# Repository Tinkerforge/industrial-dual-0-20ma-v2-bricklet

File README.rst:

Industrial Dual 0-20mA Bricklet 2.0
===================================

This repository contains the firmware source code and the hardware design
files. The documentation generator configs can be found at
https://github.com/Tinkerforge/generators

Repository Content
------------------

software/:
 * examples/: Examples for all supported languages
 * build/: Compiled files
 * src/: Source code of firmware
 * Makefile: Makefile to build project

hardware/:
 * Contains KiCad project files and additionally schematics as PDF

datasheets/:
 * Contains datasheets for sensors and complex ICs that are used

Hardware
--------

The hardware is designed with the open source EDA Suite KiCad
(http://www.kicad.org). Before you are able to open the files,
you have to install the Tinkerforge kicad-libraries
(https://github.com/Tinkerforge/kicad-libraries). You can either clone
them directly in hardware/ or clone them in a separate folder and
symlink them into hardware/
(ln -s kicad_path/kicad-libraries project_path/hardware). After that you
can open the .pro file in hardware/ with KiCad and from there view and
modify the schematics and the PCB layout.

Software
--------

If you want to do your own Brick/Bricklet firmware development we highly
recommend that you use our build environment setup script and read the
tutorial (https://www.tinkerforge.com/en/doc/Tutorials/Tutorial_Build_Environment/Tutorial.html).

To compile the C code we recommend you to install the newest GNU Arm Embedded
Toolchain (https://launchpad.net/gcc-arm-embedded/+download).
You also need to install bricklib2 (https://github.com/Tinkerforge/bricklib2).

You can either clone it directly in software/src/ or clone it in a
separate folder and symlink it into software/src/
(ln -s bricklib_path/bricklib2 project_path/software/src/). Finally make sure to
have CMake installed (http://www.cmake.org/cmake/resources/software.html).

After that you can build the firmware by invoking make in software/.
The firmware (.zbin) can then be found in software/build/ and uploaded
with brickv (click button "Flashing" on start screen).

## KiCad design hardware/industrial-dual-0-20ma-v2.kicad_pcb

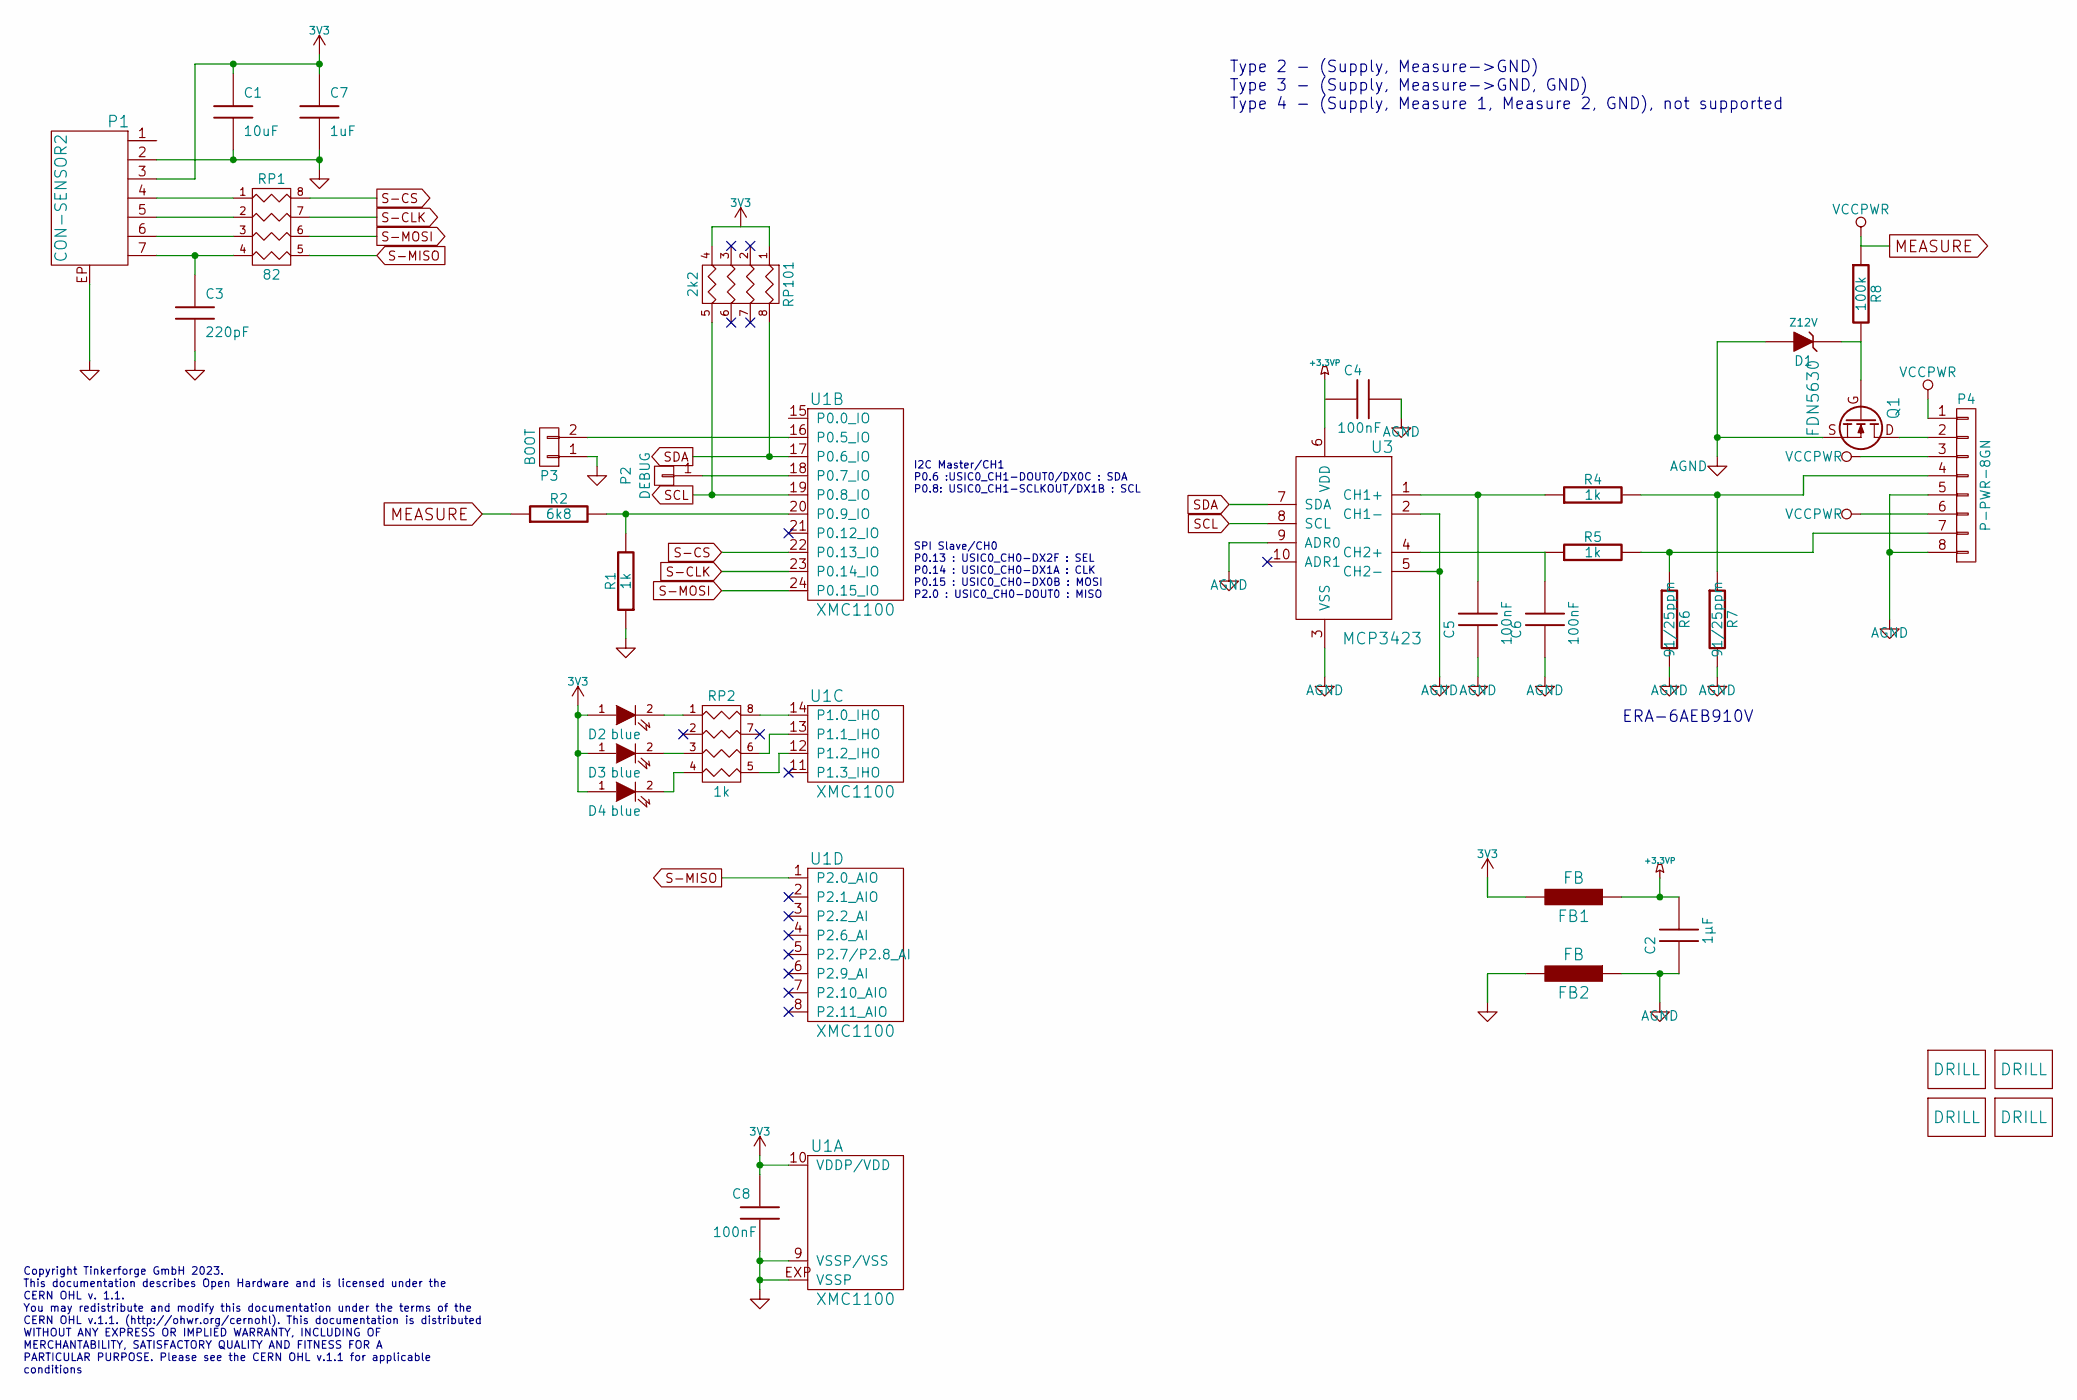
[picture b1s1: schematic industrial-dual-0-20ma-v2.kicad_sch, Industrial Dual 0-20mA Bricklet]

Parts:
C1: 10uF; C0805
C2: 1µF; C0603F
C3: 220pF; C0402F
C4, C5, C6, C8: 100nF; C0603F
C7: 1uF; C0603F
D1: Z12V; MiniMelf
D2, D3, D4: blue; D0603F
FB1, FB2: FB; C0603F
P1: CON-SENSOR2
P2: DEBUG; DEBUG_PAD
P3: BOOT; SolderJumper
P4: P-PWR-8GN; OQ_8P
Q1: FDN5630; SOT23GDS
R1, R4, R5: 1k; R0603F
R2: 6k8; R0603F
R6, R7: 91/25ppm; R0805
R8: 100k; R0603F
RP1: 82; 4X0402
RP2: 1k; 4X0603
RP101: 2k2; 4X0603
U1: XMC1100; QFN24-4x4mm-0.5mm
U3: MCP3423; MSOP10-0.5
U4, U5, U6, U7: DRILL; DRILL_NP

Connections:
3V3: C1.1, C7.1, C8.1, D2.1 (A), D3.1 (A), D4.1 (A), FB1.2, P1.3, RP101.1, RP101.4, U1.10 (VDDP/VDD)
+3.3VP: C2.2, C4.1, FB1.1, U3.6 (VDD)
AGND: C2.1, C4.2, C5.1, C6.1, D1.1 (A), FB2.1, P4.5, P4.8, Q1.S, R6.2, R7.2, U3.2 (CH1-), U3.3 (VSS), U3.5 (CH2-), U3.9 (ADR0)
GND: C1.2, C3.2, C7.2, C8.2, FB2.2, P1.2, P1.EP, P3.1, R1.1, U1.9 (VSSP/VSS), U1.EXP (VSSP)
MEASURE: P4.1, P4.3, P4.6, R2.1, R8.1
unnamed: C3.1, P1.7, RP1.4
unnamed: C5.2, R4.1, U3.1 (CH1+)
unnamed: C6.2, R5.1, U3.4 (CH2+)
unnamed: D1.2 (K), Q1.G, R8.2
unnamed: D2.2 (K), RP2.1
unnamed: D3.2 (K), RP2.3
unnamed: D4.2 (K), RP2.4
unnamed: P1.4, RP1.1
unnamed: P1.5, RP1.2
unnamed: P1.6, RP1.3
unnamed: P2.1, U1.18 (P0.7_IO)
unnamed: P3.2, U1.16 (P0.5_IO)
unnamed: P4.2, Q1.D
unnamed: P4.4, R4.2, R7.1
unnamed: P4.7, R5.2, R6.1
unnamed: R1.2, R2.2, U1.20 (P0.9_IO)
unnamed: RP2.5 (R4), U1.12 (P1.2_IHO)
unnamed: RP2.6 (R3), U1.13 (P1.1_IHO)
unnamed: RP2.8 (R1), U1.14 (P1.0_IHO)
S-CLK: RP1.7 (R2), U1.23 (P0.14_IO)
S-CS: RP1.8 (R1), U1.22 (P0.13_IO)
S-MISO: RP1.5 (R4), U1.1 (P2.0_AIO)
S-MOSI: RP1.6 (R3), U1.24 (P0.15_IO)
SCL: RP101.5 (R4), U1.19 (P0.8_IO), U3.8 (SCL)
SDA: RP101.8 (R1), U1.17 (P0.6_IO), U3.7 (SDA)

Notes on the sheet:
Type 2 - (Supply, Measure->GND) Type 3 - (Supply, Measure->GND, GND) Type 4 - (Supply, Measure 1, Measure 2, GND), not supported
SPI Slave/CH0 P0.13 : USIC0_CH0-DX2F : SEL P0.14 : USIC0_CH0-DX1A : CLK P0.15 : USIC0_CH0-DX0B : MOSI P2.0 : USIC0_CH0-DOUT0 : MISO
ERA-6AEB910V
Copyright Tinkerforge GmbH 2023. This documentation describes Open Hardware and is licensed under the CERN OHL v. 1.1. You may redistribute and modify this documentation under the terms of the CERN OHL v.1.1. (http://ohwr.org/cernohl). This documentation is distributed WITHOUT ANY EXPRESS OR IMPLIE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
I2C Master/CH1 P0.6 :USIC0_CH1-DOUT0/DX0C : SDA P0.8: USIC0_CH1-SCLKOUT/DX1B : SCL

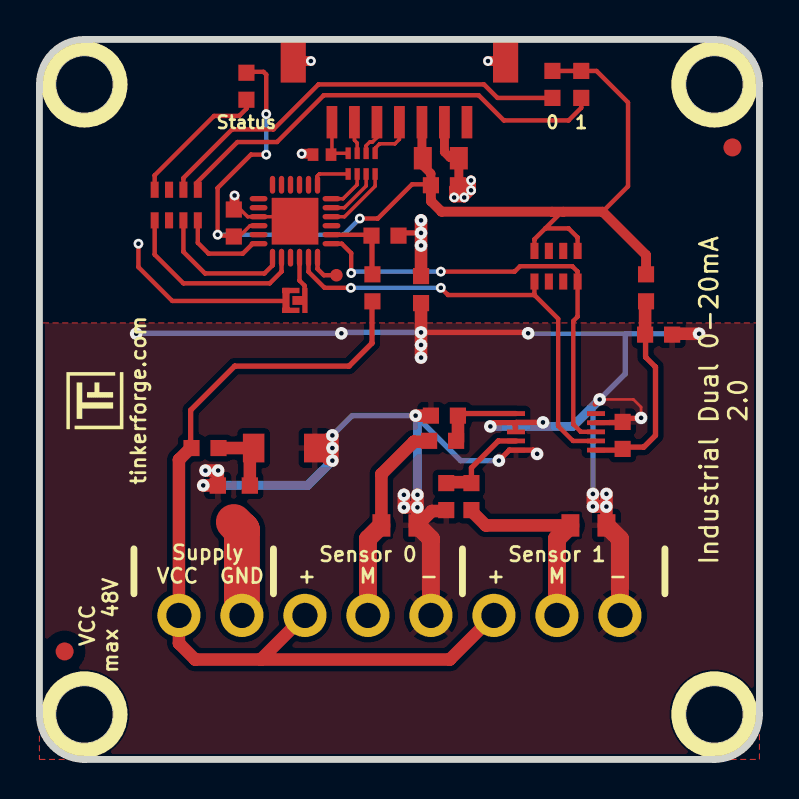
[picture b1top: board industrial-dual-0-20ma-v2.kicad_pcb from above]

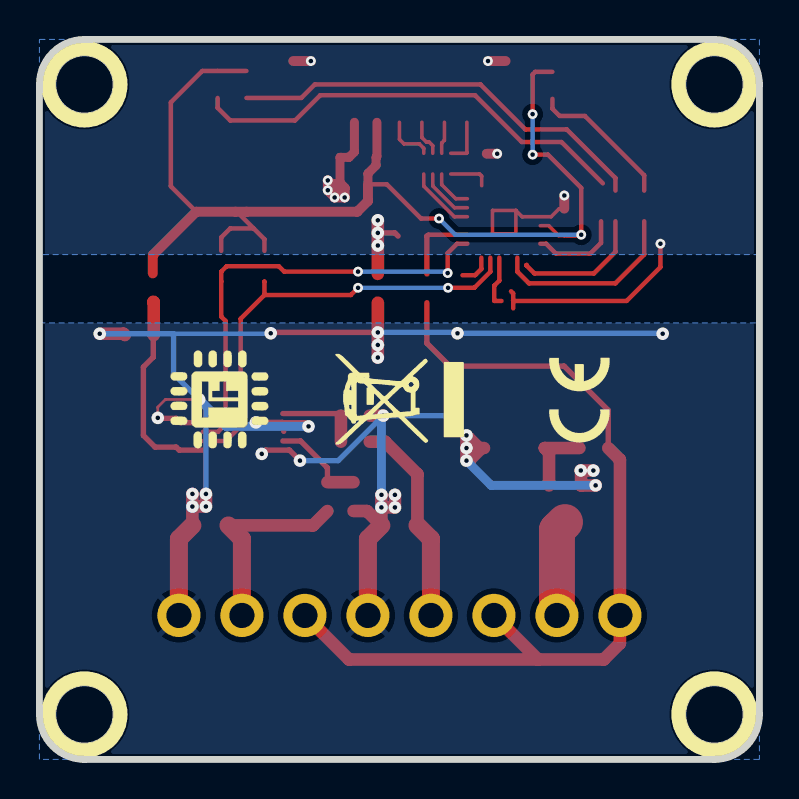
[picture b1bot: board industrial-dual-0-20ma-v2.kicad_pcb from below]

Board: 2 copper layers, 40.0 x 40.0 mm, 39 parts (2 on the bottom side), 30 nets.

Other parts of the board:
Fiducial_Mark: VAL**; Fiducial_Mark
Fiducial_Mark#2: VAL**; Fiducial_Mark
VAL: CE_5mm
VAL#2: WEEE_7mm

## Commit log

2018-02-22 Add datasheet
2018-02-22 Add schematic
2018-02-22 Add layout
2018-02-22 Assign footprints
2018-02-23 Add .gitignore
2018-03-13 Fix position of silkscreen text
2018-03-13 Fix font size
2018-03-19 add two status leds, fix logo positions, fix text
2018-03-19 fix status text
2018-03-19 fix product name
2018-04-26 Add initial firmware
2018-04-26 Rename channel based callback value support code
2018-05-02 add missing pullup
2018-05-02 Functional firmware but value calculation pending
2018-05-02 Rename info LED to channel LED
2018-05-02 Remove unused define
2018-05-02 Define channel count
2018-05-02 Channel based defines are in config.h
2018-05-07 Move callback value type definition to config.h
2018-05-11 Rename files
2018-05-15 hardware: Remove special library
2018-05-18 Partial firmware implementation. Channel LED features are pending
2018-06-06 Adapt to bricklib2 callback-value changes to fix wrong threshold min/max type
2018-06-11 Add return statement
2018-06-14 Implementation of channel status LED control
2018-06-18 Change footprints to x0402F/x0603F
2018-06-28 Fix readme
2018-07-11 Add Makefile with docker support
2018-07-11 Remove obsolete generate_makefile scripts
2018-07-11 Update directory structure and build instructions
2018-07-17 specify processor
2018-07-19 Use intensity with 4-20mA range as default
2018-07-24 Add reverse logic for channel status LEDs
2018-07-26 Remove duplicate line
2018-07-31 Add PDF schematic
2018-07-31 Add 3d model (*.FCStd & *.step)
2018-08-01 Add examples
2018-09-14 vbnet: Fix typo in comment
2018-10-02 Add BOOTLOADER_FIX_POINTER_END define
2018-10-04 Add rev to changelog
2018-10-16 Remove in-development marker
2018-11-06 Add rust examples
2018-11-07 rust: Accept host names for ip connection, fix naming inconsistencies
2018-11-07 rust: Rename callback receivers.
2018-12-05 Fix typo in threshold example
2018-12-05 Fix typo in simple example
2018-12-14 Add go examples.
2018-12-14 go: Fix printf parameters.
2018-12-18 go: Change import path.
2018-12-18 go: Change import path again.
2018-12-20 rust: Fix result variable names in examples.
2019-01-24 mqtt: Add examples.
2019-01-24 mqtt: Fix example header.
2019-01-24 mqtt: Remove executable bit in example permissions.
2019-01-24 go: Minor example fixes.
2019-01-24 mqtt: Minor example fixes.
2019-02-25 Fix typo
2019-03-25 mqtt: Fix example whitespace.
2019-03-28 mqtt: Fix whitespace.
2019-05-29 Increase version for new release (changes in bricklib2)
2019-08-22 c: Adapt to bindings changes
2020-01-13 examples: Use python3 input instead of python2 raw_input.
2020-01-13 examples: mqtt: Remove trailing whitespace.
2020-06-10 Add missing invalid-parameter check for set-sample-rate and set-gain functions
2020-06-10 Add commit ref to changelog
2020-08-19 Add uc examples.
2020-08-25 uc: Fix whitespace
2020-08-27 uc: Fix warnings.
2020-08-31 uc: Use fixed-with placeholders in format strings.
2020-09-02 uc: Add example driver note.
2020-10-16 uc: Fix divisor type.
2021-10-25 Update KiCad link
    https://www.kicad.org/blog/2021/10/Avoid-links-to-former-kicad-domain/
2022-01-05 specify processor as XMC1100
2022-04-19 examples: uc: Rename TF_HalContext to TF_HAL.
2022-04-27 uc: Adapt to bindings changes
2022-07-06 Add license files.
2022-12-30 fix schematic, move to kicad6
2023-01-27 remove old files
2023-01-27 Data Cleanup

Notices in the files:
hardware/industrial-dual-0-20ma-v2.kicad_pcb:
Licensed under CERN OHL v.1.1
Copyright (©) 2023, T.Schneidermann
